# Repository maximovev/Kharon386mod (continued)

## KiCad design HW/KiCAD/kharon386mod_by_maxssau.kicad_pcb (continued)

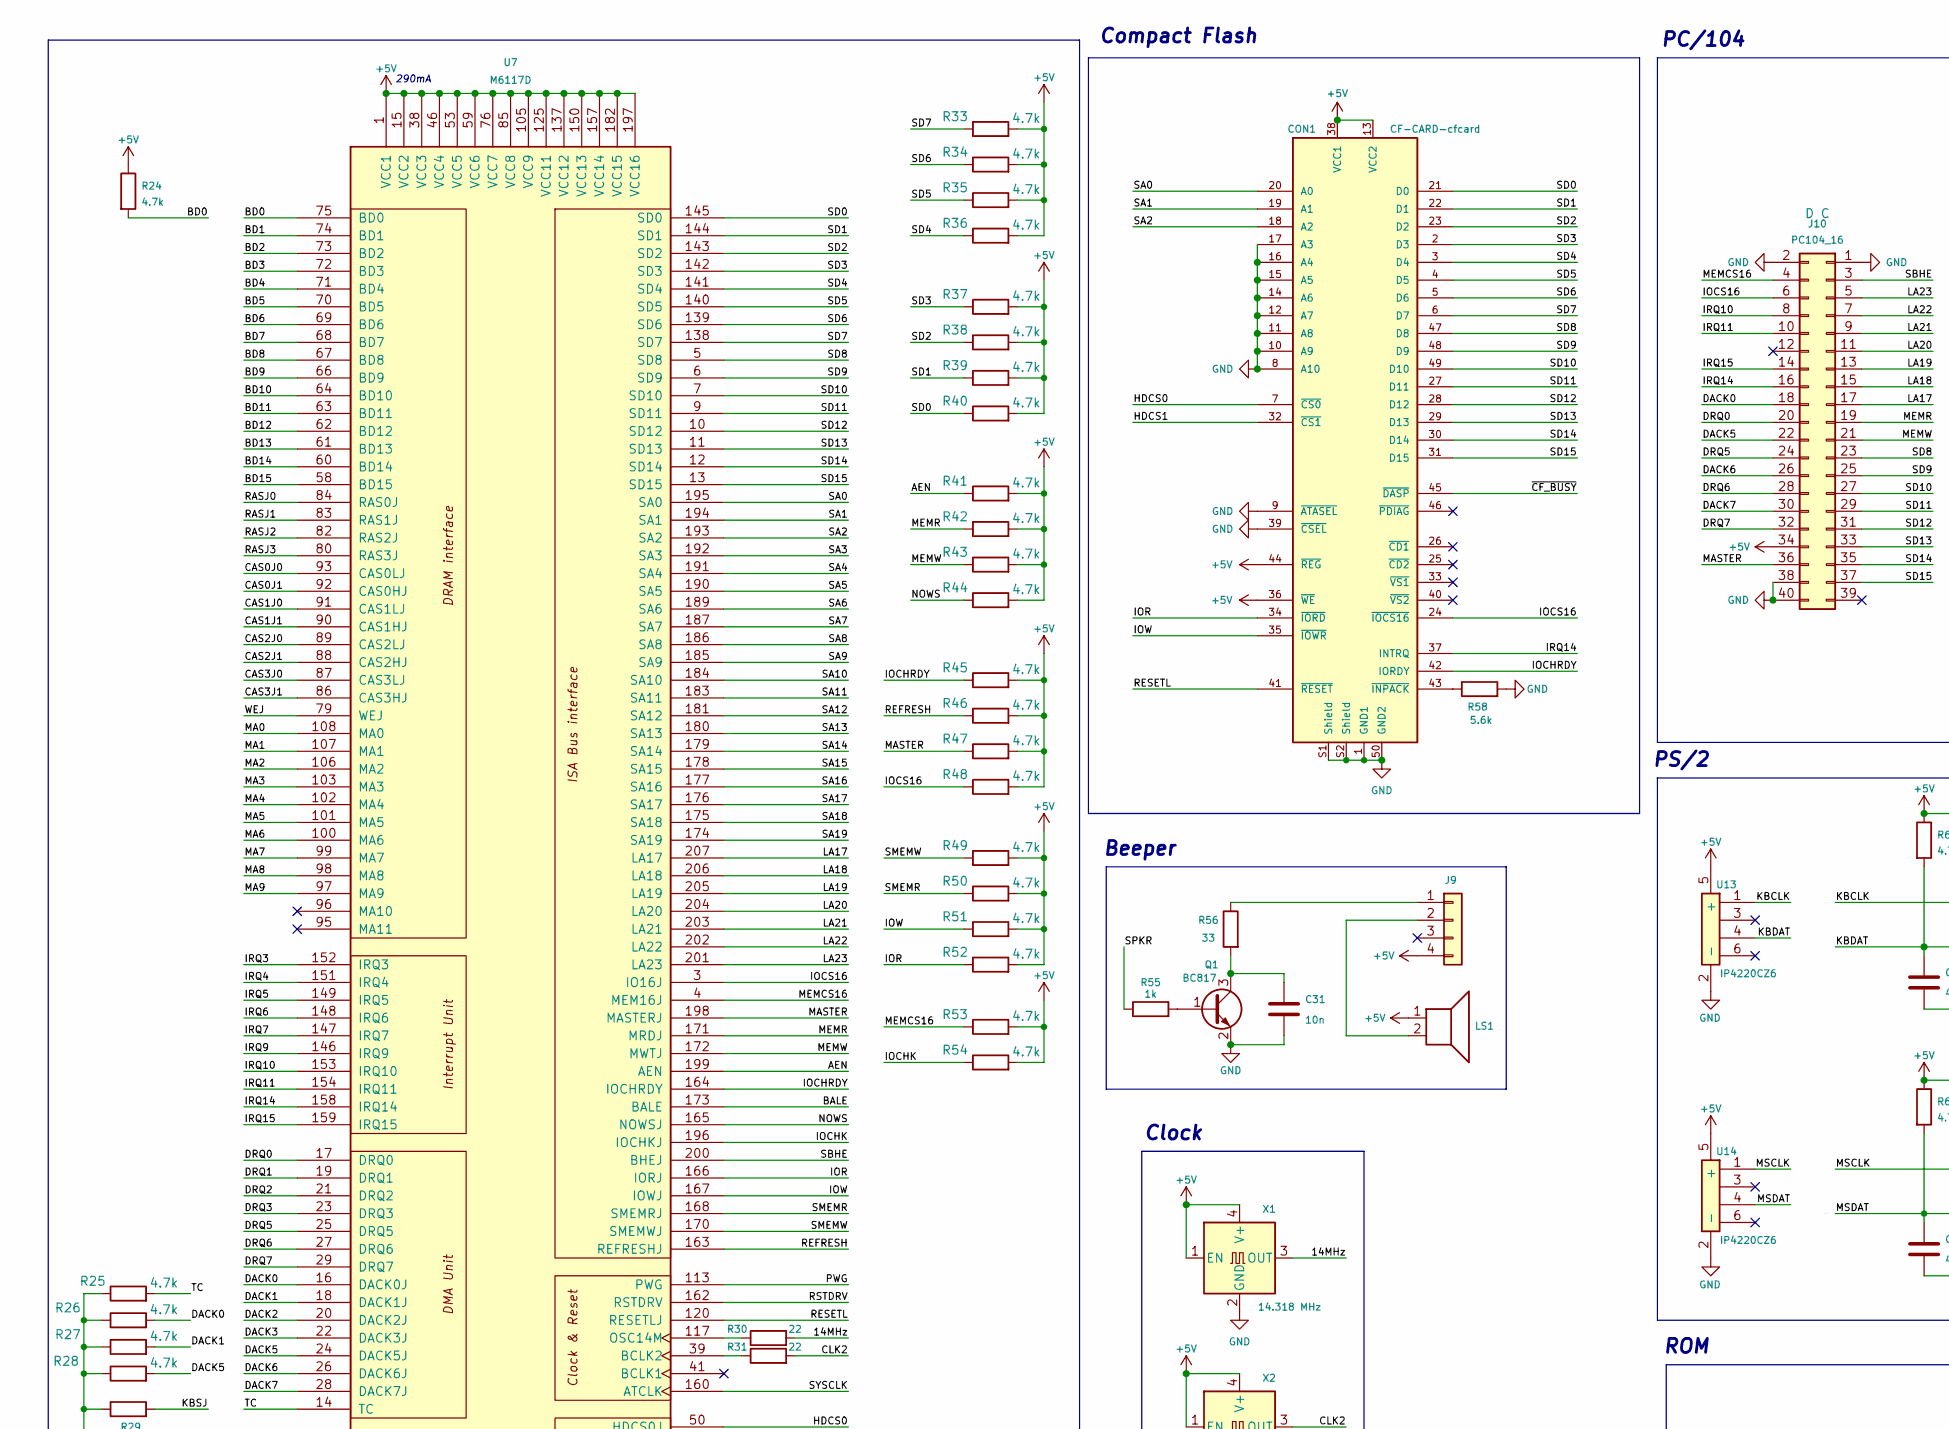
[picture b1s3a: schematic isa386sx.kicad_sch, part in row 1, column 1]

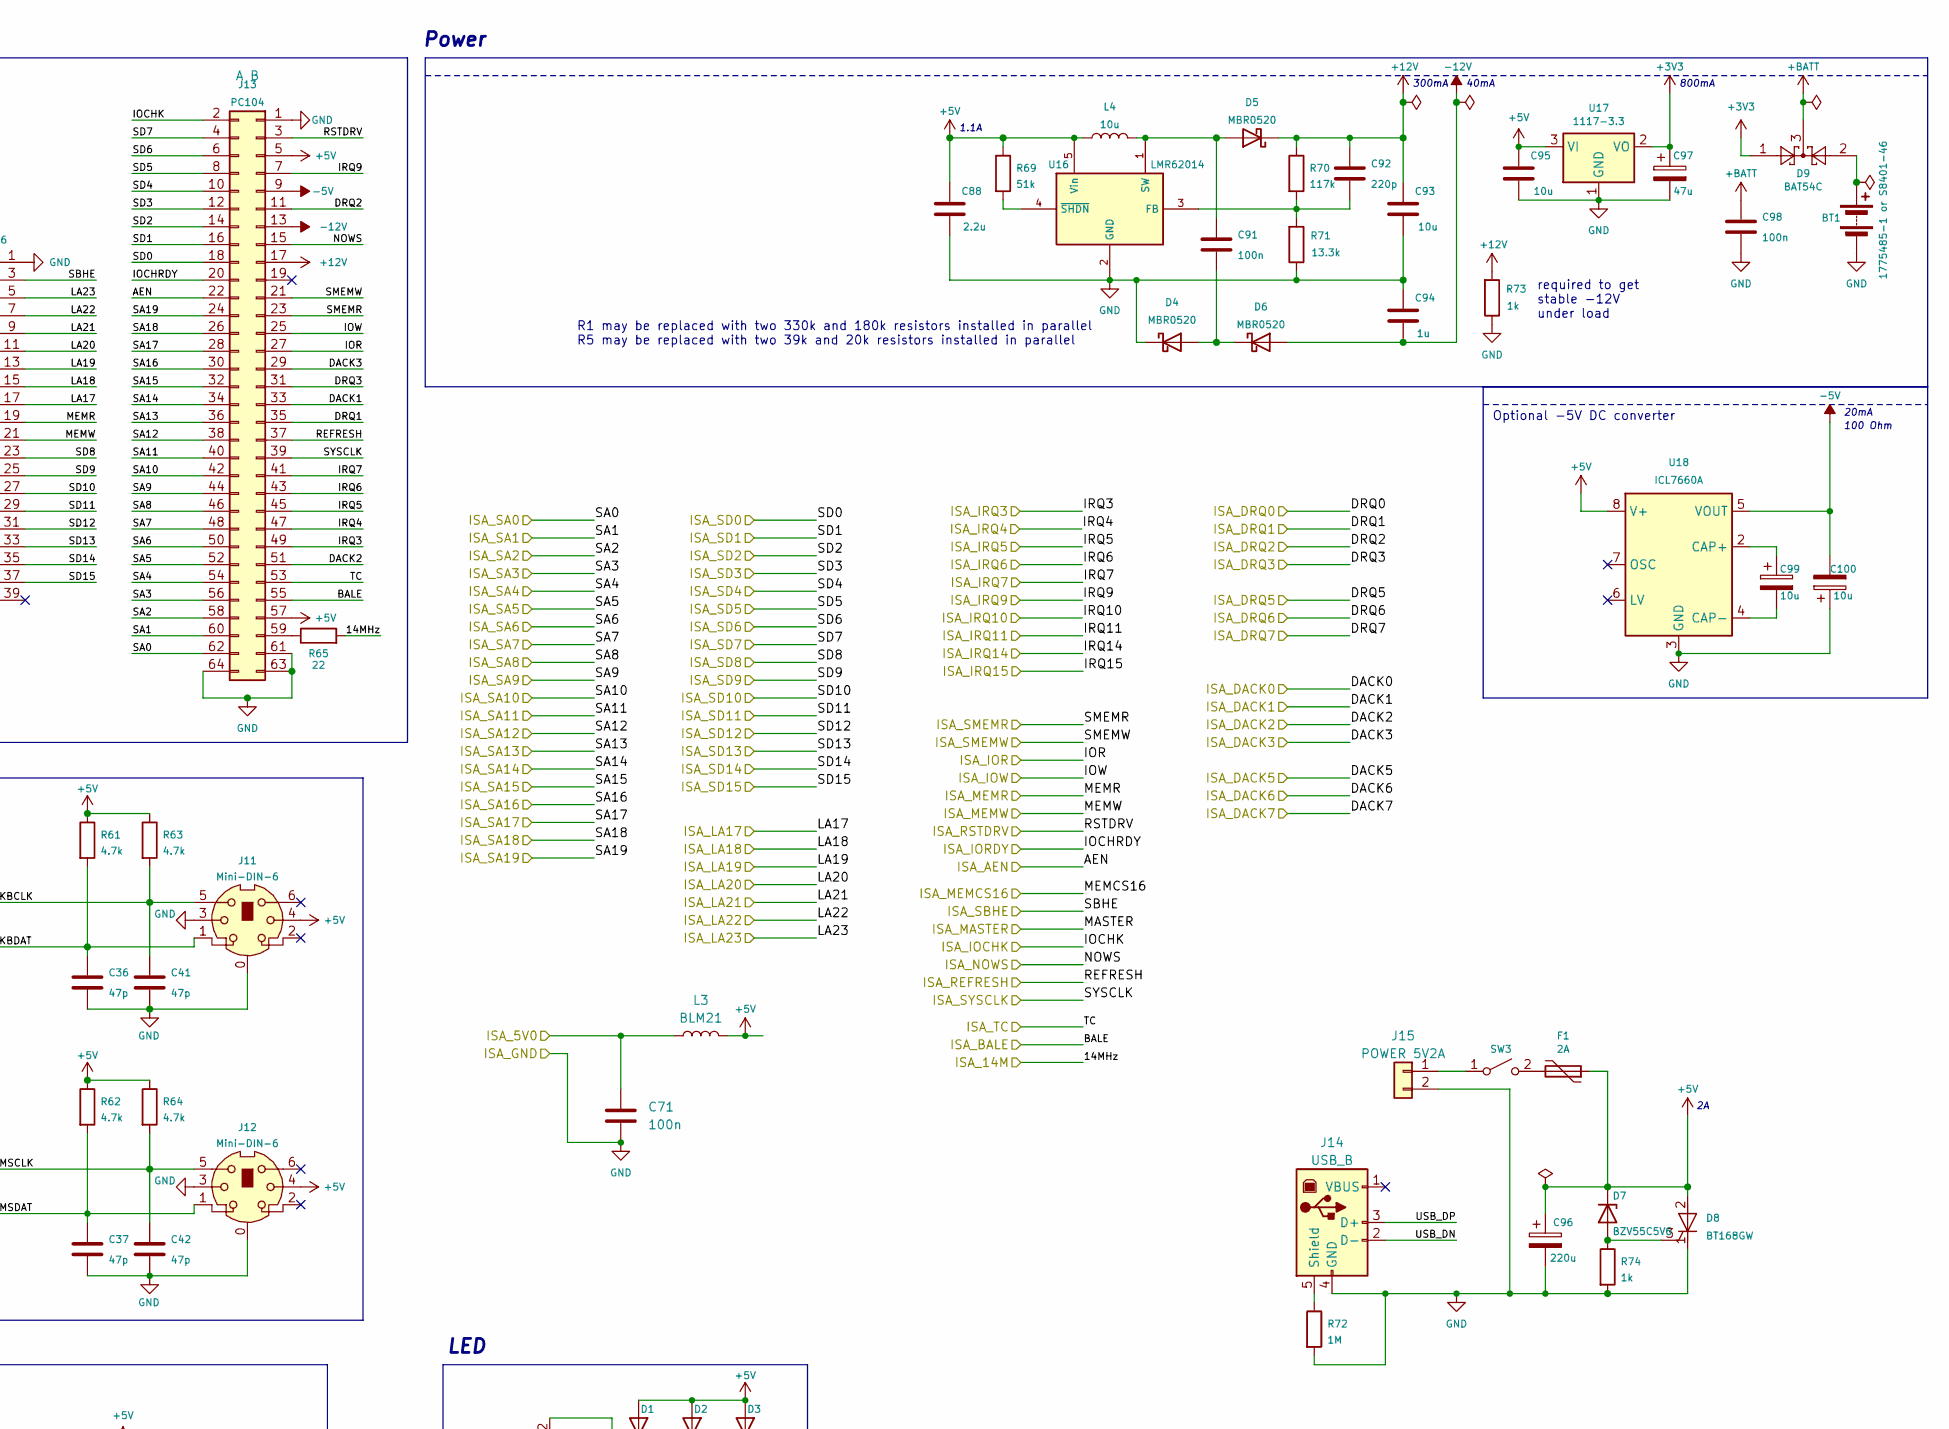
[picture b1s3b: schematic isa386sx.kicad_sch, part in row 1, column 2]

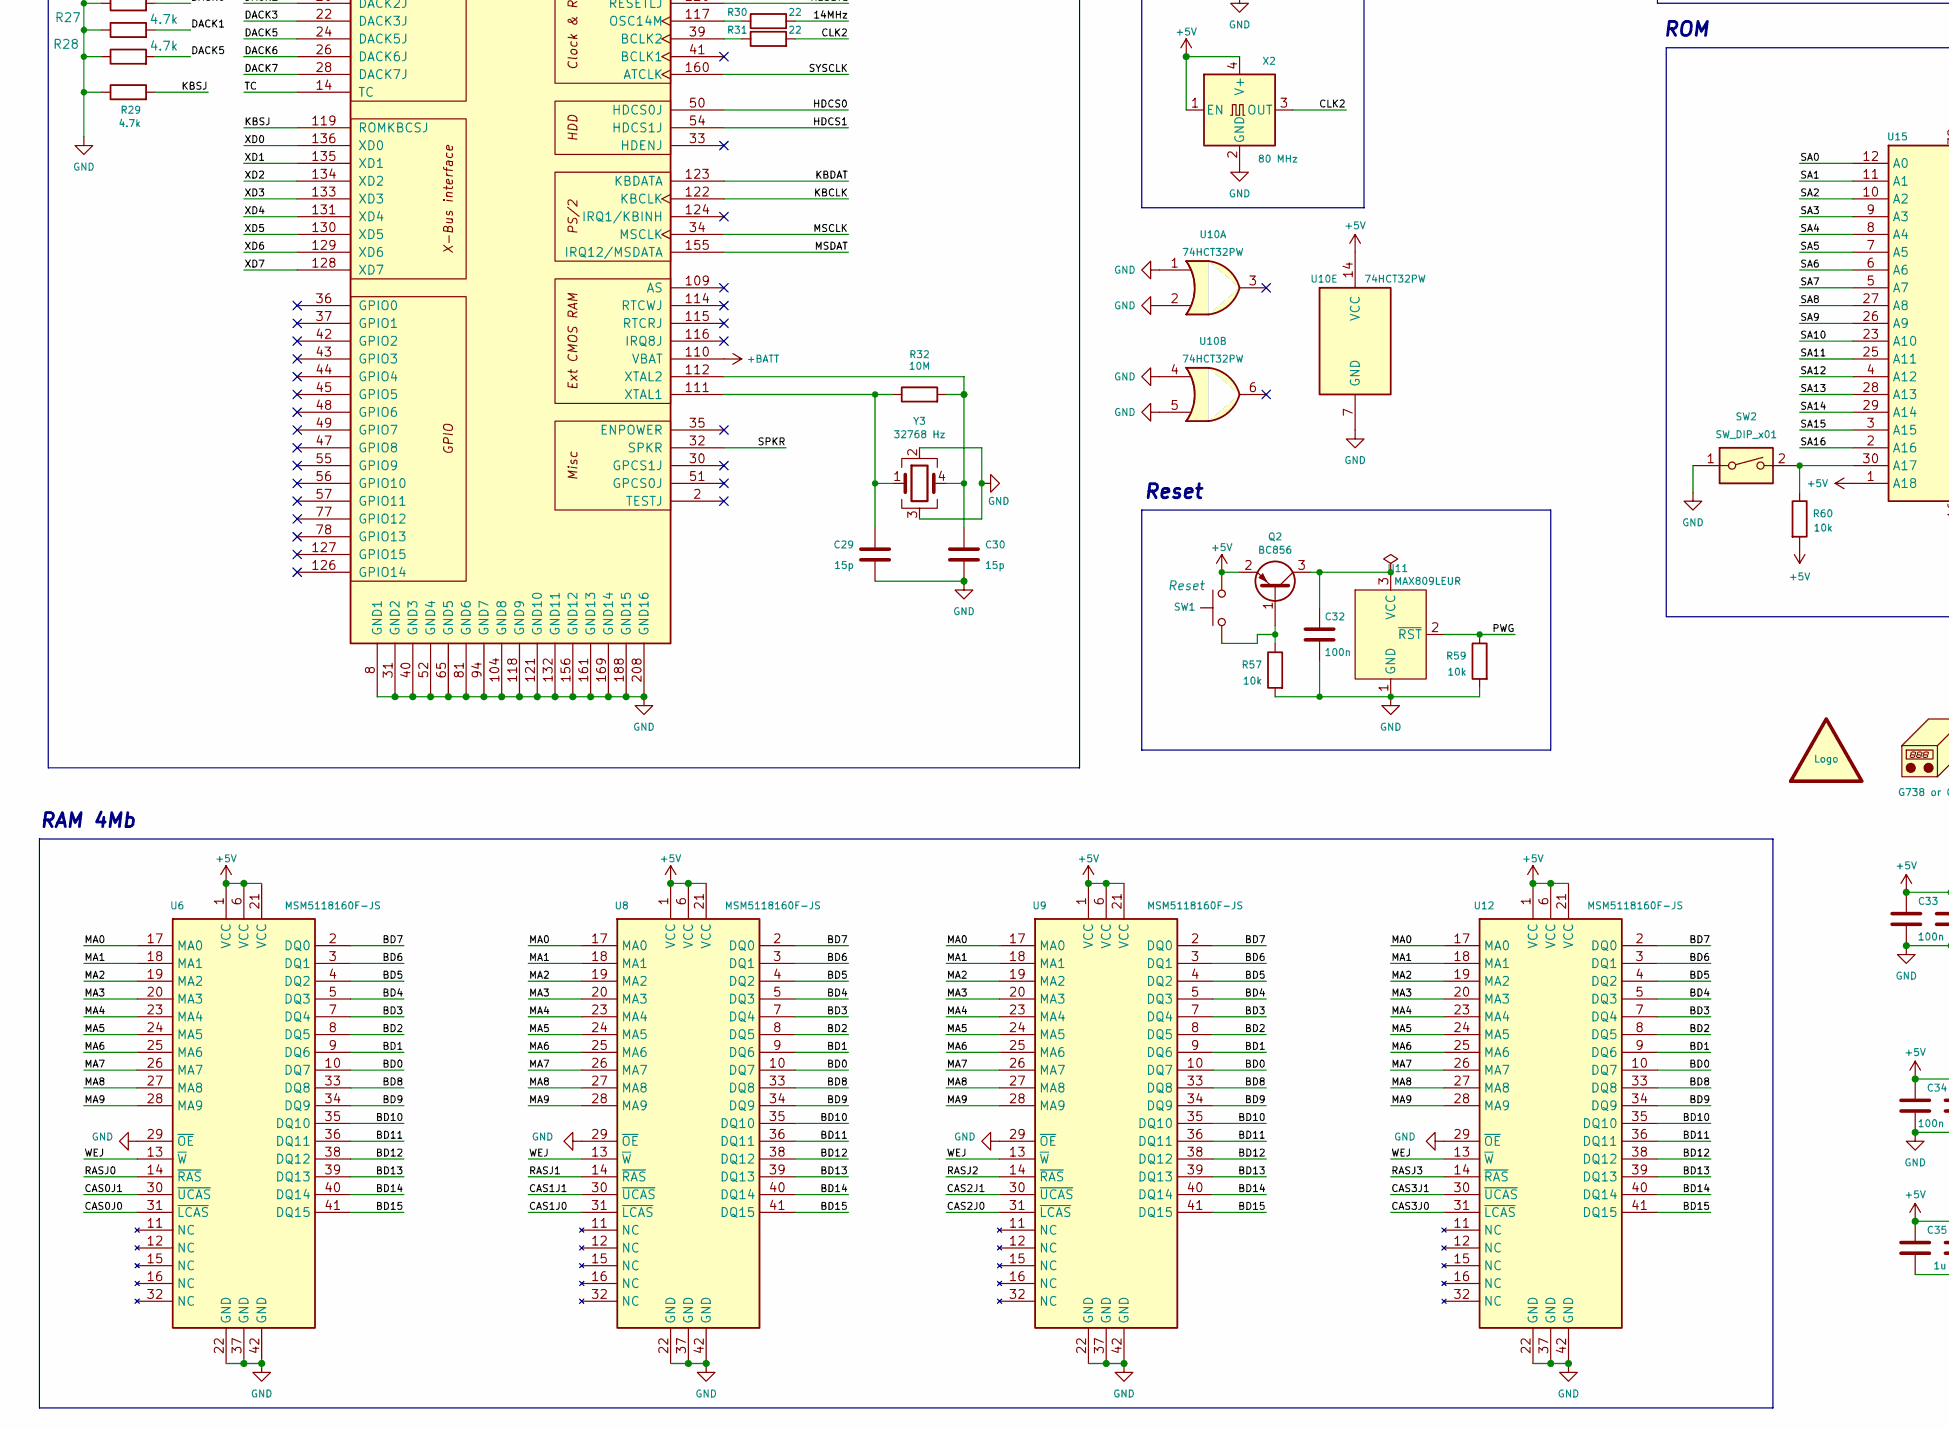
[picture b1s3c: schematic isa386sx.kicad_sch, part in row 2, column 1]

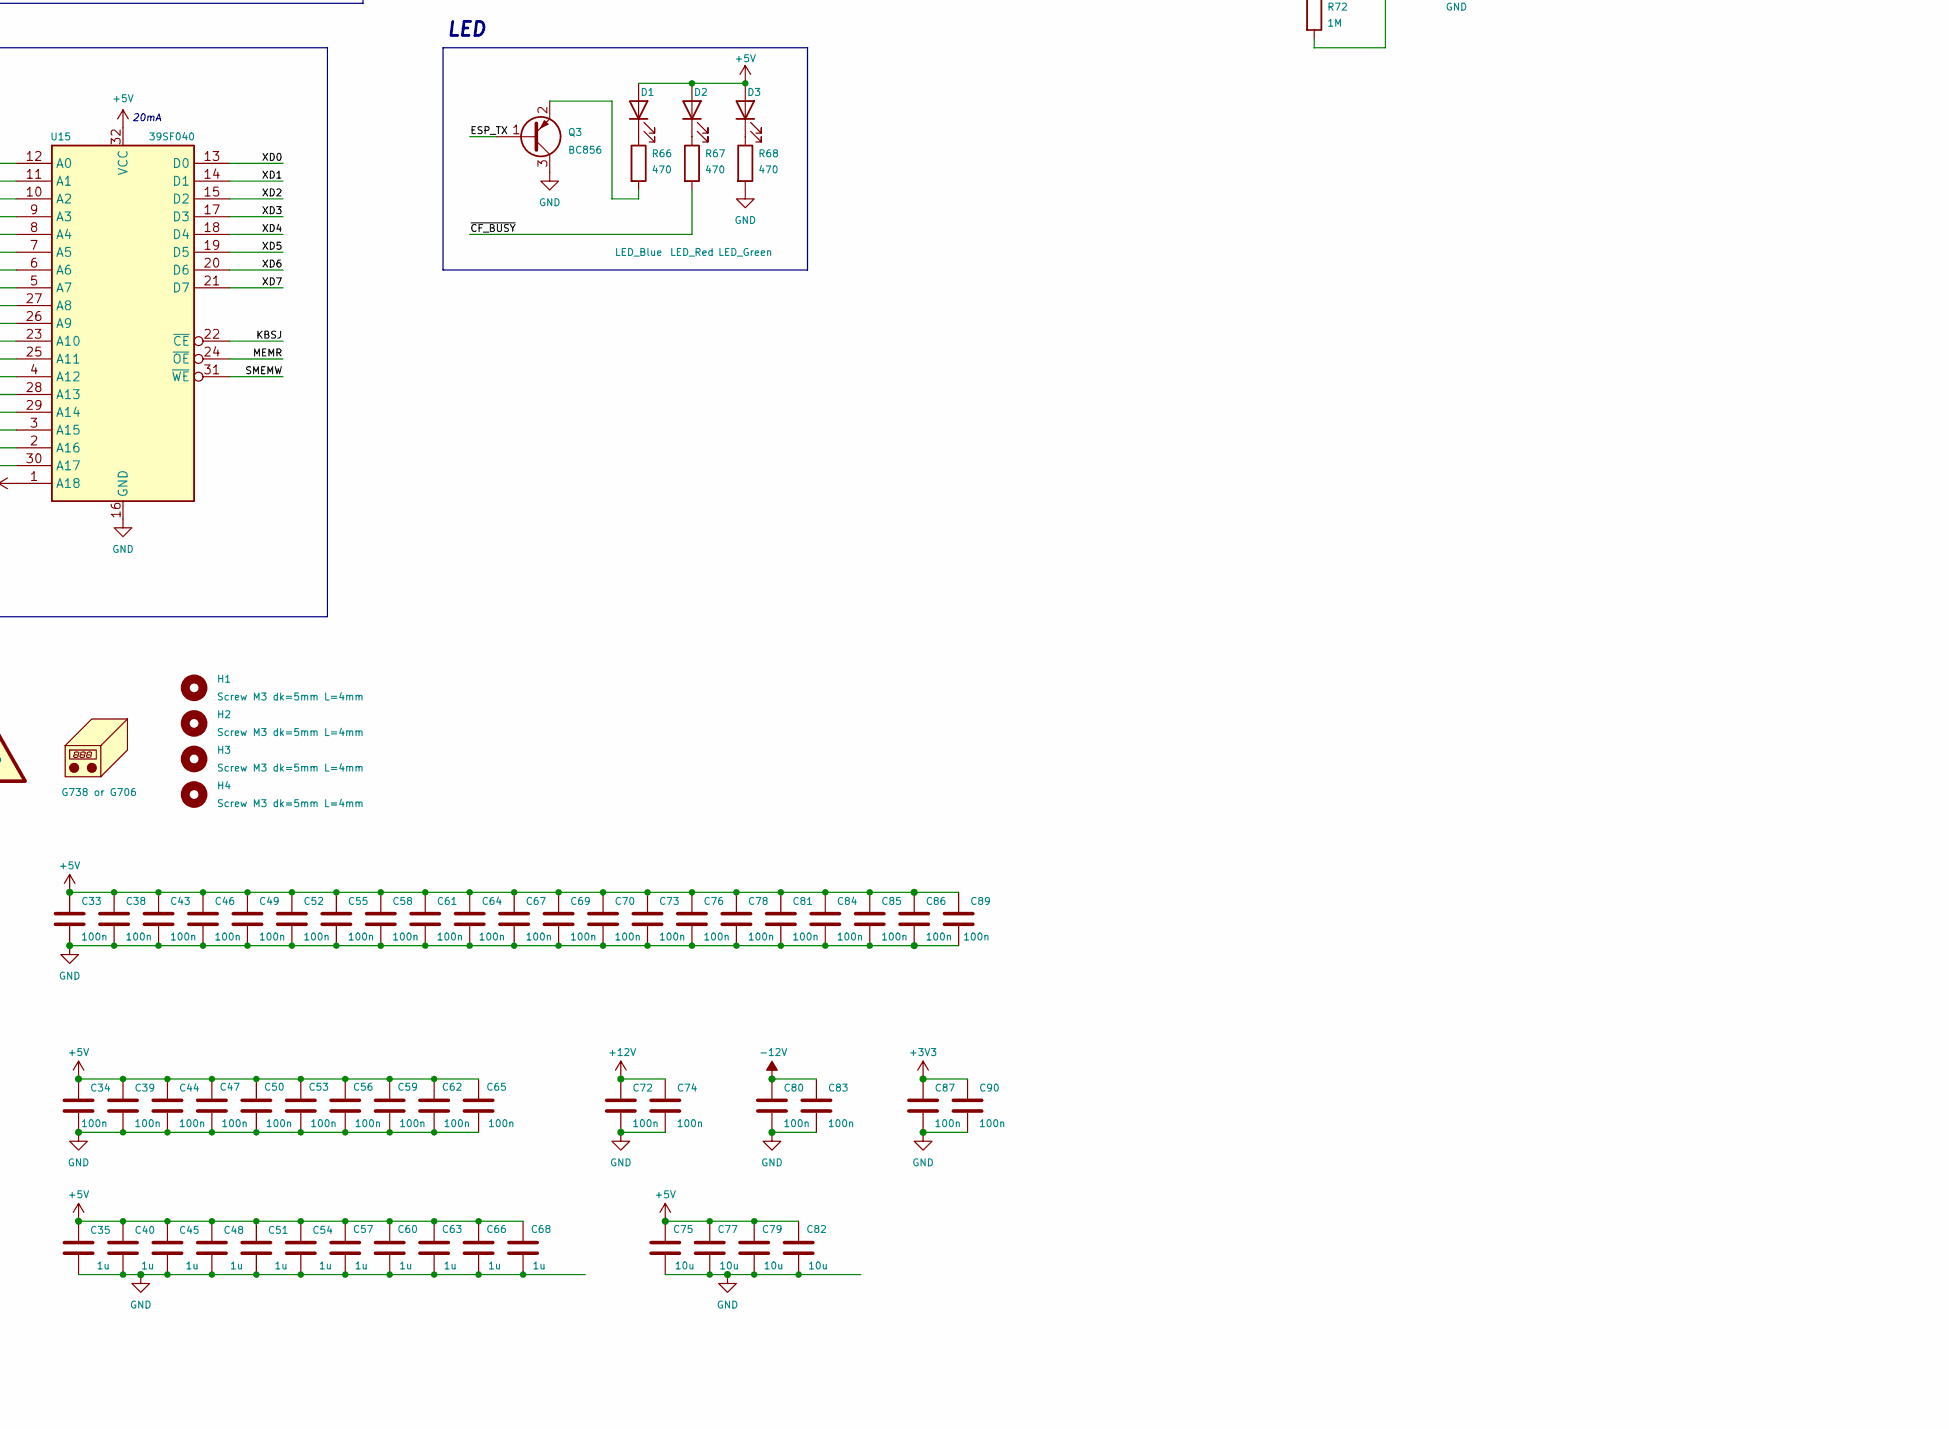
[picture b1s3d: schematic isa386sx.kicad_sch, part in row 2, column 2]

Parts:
BT1: 1775485-1 or S8401-46; BatteryHolder_MYOUNG_BS-07-A1BJ001_CR2032
C29, C30: 15p; C_0805_2012Metric_Pad1.18x1.45mm_HandSolder
C31: 10n; C_0805_2012Metric_Pad1.18x1.45mm_HandSolder
C32, C33, C34, C38, C39, C43, C44, C46, C47, C49, C50, C52, C53, C55, C56, C58, C59, C61, C62, C64, C65, C67, C69, C70, C71, C72, C73, C74, C76, C78, C80, C81, C83, C84, C85, C86, C87, C89, C90, C91, C98: 100n; C_0805_2012Metric_Pad1.18x1.45mm_HandSolder
C35, C40, C45, C48, C51, C54, C57, C60, C63, C66, C68, C94: 1u; C_0805_2012Metric_Pad1.18x1.45mm_HandSolder
C36, C37, C41, C42: 47p; C_0805_2012Metric_Pad1.18x1.45mm_HandSolder
C75, C77, C79, C82, C93, C95: 10u; C_0805_2012Metric_Pad1.18x1.45mm_HandSolder
C88: 2.2u; C_0805_2012Metric_Pad1.18x1.45mm_HandSolder
C92: 220p; C_0805_2012Metric_Pad1.18x1.45mm_HandSolder
C96: 220u; CP_EIA-7343-31_Kemet-D_Pad2.25x2.55mm_HandSolder
C97: 47u; CP_EIA-7343-31_Kemet-D_Pad2.25x2.55mm_HandSolder
C99, C100: 10u; CP_EIA-3528-21_Kemet-B_Pad1.50x2.35mm_HandSolder
CON1: CF-CARD-cfcard; TE_1734451-1-LONG
D1: LED_Blue; LED_D3.0mm_Horizontal_O1.27mm_Z6.0mm
D2: LED_Red; LED_D3.0mm_Horizontal_O1.27mm_Z6.0mm
D3: LED_Green; LED_D3.0mm_Horizontal_O1.27mm_Z6.0mm
D4, D5, D6: MBR0520; D_SOD-123
D7: BZV55C5V6; D_MiniMELF
D8: BT168GW; SOT-223-3_TabPin2
D9: BAT54C; SOT-23
F1: 2A; Fuse_1812_4532Metric_Pad1.30x3.40mm_HandSolder
H1, H2, H3, H4: Screw M3 dk=5mm L=4mm; MountingHole_3.2mm_M3_dk5.2mm_Mask
J9: Conn_01x04; PinHeader_1x04_P2.54mm_Vertical
J10: PC104_16; PinSocket_2x20_P2.54mm_Vertical
J11, J12: Mini-DIN-6; minidin-6
J13: PC104; PinSocket_2x32_P2.54mm_Vertical
J14: USB_B; USB_B_Lumberg_2411_02_Horizontal
J15: POWER 5V2A; TerminalBlock_bornier-2_P5.08mm
L3: BLM21; L_1210_3225Metric_Pad1.42x2.65mm_HandSolder
L4: 10u; L_7.3x7.3_H4.5
LOGO1: graphic; black-mage-12.5x8.6
LS1: Speaker; Buzzer_12x9.5RM7.6
N1: G738 or G706; G738
Q1: BC817; SOT-23
Q2, Q3: BC856; SOT-23
R24, R25, R26, R27, R28, R29, R33, R34, R35, R36, R37, R38, R39, R40, R41, R42, R43, R44, R45, R46, R47, R48, R49, R50, R51, R52, R53, R54, R61, R62, R63, R64: 4.7k; R_0805_2012Metric_Pad1.20x1.40mm_HandSolder
R30, R31, R65: 22; R_0805_2012Metric_Pad1.20x1.40mm_HandSolder
R32: 10M; R_0805_2012Metric_Pad1.20x1.40mm_HandSolder
R55, R73, R74: 1k; R_0805_2012Metric_Pad1.20x1.40mm_HandSolder
R56: 33; R_0805_2012Metric_Pad1.20x1.40mm_HandSolder
R57, R59, R60: 10k; R_0805_2012Metric_Pad1.20x1.40mm_HandSolder
R58: 5.6k; R_0805_2012Metric_Pad1.20x1.40mm_HandSolder
R66, R67, R68: 470; R_0805_2012Metric_Pad1.20x1.40mm_HandSolder
R69: 51k; R_0805_2012Metric_Pad1.20x1.40mm_HandSolder
R70: 117k; R_0805_2012Metric_Pad1.20x1.40mm_HandSolder
R71: 13.3k; R_0805_2012Metric_Pad1.20x1.40mm_HandSolder
R72: 1M; R_0805_2012Metric_Pad1.20x1.40mm_HandSolder
SW1: SW_Push; SW_Tactile_SPST_Angled_PTS645Vx83-2LFS
SW2: SW_DIP_x01; SW_DIP_SPSTx01_Slide_6.7x4.1mm_W7.62mm_P2.54mm_LowProfile
SW3: Jumper / Pin header 1x2 Pitch=2.54mm; Molex_KK-254_AE-6410-02A_1x02_P2.54mm_Vertical
U6, U8, U9, U12: MSM5118160F-JS; SOJ-42
U7: M6117D; PQFP-208_28x28mm_P0.5mm
U10: 74HCT32PW; TSSOP-14_4.4x5mm_P0.65mm
U11: MAX809LEUR; SOT-23
U13, U14: IP4220CZ6; TSOP-6_1.65x3.05mm_P0.95mm
U15: 39SF040; PLCC-32_11.4x14.0mm_P1.27mm-longpads
U16: LMR62014; SOT-23-5_HandSoldering
U17: 1117-3.3; SOT-223-3_TabPin2
U18: ICL7660A; SOIC-8_3.9x4.9mm_P1.27mm
X1: 14.318 MHz; Oscillator_SMD_Abracon_ASE-4Pin_3.2x2.5mm_HandSoldering
X2: 80 MHz; Oscillator_SMD_Abracon_ASE-4Pin_3.2x2.5mm_HandSoldering
Y3: 32768 Hz; Crystal_SMD_SeikoEpson_MC306-4Pin_8.0x3.2mm_HandSoldering

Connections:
+3V3: C87.2, C90.2, C97.1, D9.1, U17.2 (VO); also elsewhere on the board
+5V: C33.2, C34.2, C35.2, C38.2, C39.2, C40.2, C43.2, C44.2, C45.2, C46.2, C47.1, C48.2, C49.2, C50.1, C51.2, C52.2, C53.1, C54.2, C55.2, C56.1, C57.1, C58.2, C59.1, C60.1, C61.2, C62.1, C63.1, C64.2, C65.1, C66.1, C67.2, C68.1, C69.2, C70.2, C73.2, C75.1, C76.2, C77.1, C78.2, C79.1, C81.2, C82.1, C84.2, C85.2, C86.2, C88.2, C89.2, C95.2, C96.1, CON1.13 (VCC2), CON1.36 (~WE), CON1.38 (VCC1), CON1.44 (~REG), D1.2 (A), D2.2 (A), D3.2 (A), D7.1 (K), D8.2 (A), F1.1, J9.4, J10.34, J11.4, J12.4, J13.5, J13.57, L3.2, L4.1, LS1.1, Q2.2 (E), R24.1, R33.2, R34.2, R35.2, R36.2, R37.2, R38.2, R39.2, R40.2, R41.2, R42.2, R43.2, R44.2, R45.2, R46.2, R47.2, R48.2, R49.2, R50.2, R51.2, R52.2, R53.2, R54.2, R60.2, R61.1, R62.1, R63.1, R64.1, R69.1, SW1.1, U6.1 (VCC), U6.6 (VCC), U6.21 (VCC), U7.1 (VCC1), U7.15 (VCC2), U7.38 (VCC3), U7.46 (VCC4), U7.53 (VCC5), U7.59 (VCC6), U7.76 (VCC7), U7.85 (VCC8), U7.105 (VCC9), U7.125 (VCC11), U7.137 (VCC12), U7.150 (VCC13), U7.157 (VCC14), U7.182 (VCC15), U7.197 (VCC16), U8.1 (VCC), U8.6 (VCC), U8.21 (VCC), U9.1 (VCC), U9.6 (VCC), U9.21 (VCC), U10.14 (VCC), U12.1 (VCC), U12.6 (VCC), U12.21 (VCC), U13.5 (+), U14.5 (+), U15.1 (A18), U15.32 (VCC), U16.5 (Vin), U17.3 (VI), U18.8 (V+), X1.1 (EN), X1.4 (V+), X2.1 (EN), X2.4 (V+); also elsewhere on the board
+12V: C72.2, C74.2, C92.1, C93.2, D5.1 (K), J13.17, R70.1, R73.2; also elsewhere on the board
+BATT: C98.1, D9.3, U7.110 (VBAT)
-5V: C100.2, J13.9, U18.5 (VOUT)
-12V: C80.2, C83.2, C94.1, D6.2 (A), J13.13; also elsewhere on the board
/B_ISA_5V0: C71.1, L3.1; also elsewhere on the board
/B_ISA_14M: R30.2, R65.2, X1.3 (OUT); also elsewhere on the board
/B_ISA_A0: CON1.20 (A0), J13.62, U7.195 (SA0), U15.12 (A0); also elsewhere on the board
/B_ISA_A1: CON1.19 (A1), J13.60, U7.194 (SA1), U15.11 (A1); also elsewhere on the board
/B_ISA_A2: CON1.18 (A2), J13.58, U7.193 (SA2), U15.10 (A2); also elsewhere on the board
/B_ISA_A3: J13.56, U7.192 (SA3), U15.9 (A3); also elsewhere on the board
/B_ISA_A4: J13.54, U7.191 (SA4), U15.8 (A4); also elsewhere on the board
/B_ISA_A5: J13.52, U7.190 (SA5), U15.7 (A5); also elsewhere on the board
/B_ISA_A6: J13.50, U7.189 (SA6), U15.6 (A6); also elsewhere on the board
/B_ISA_A7: J13.48, U7.187 (SA7), U15.5 (A7); also elsewhere on the board
/B_ISA_A8: J13.46, U7.186 (SA8), U15.27 (A8); also elsewhere on the board
/B_ISA_A9: J13.44, U7.185 (SA9), U15.26 (A9); also elsewhere on the board
/B_ISA_A10: J13.42, U7.184 (SA10), U15.23 (A10); also elsewhere on the board
/B_ISA_A11: J13.40, U7.183 (SA11), U15.25 (A11); also elsewhere on the board
/B_ISA_A12: J13.38, U7.181 (SA12), U15.4 (A12); also elsewhere on the board
/B_ISA_A13: J13.36, U7.180 (SA13), U15.28 (A13); also elsewhere on the board
/B_ISA_A14: J13.34, U7.179 (SA14), U15.29 (A14); also elsewhere on the board
/B_ISA_A15: J13.32, U7.178 (SA15), U15.3 (A15); also elsewhere on the board
/B_ISA_A16: J13.30, U7.177 (SA16), U15.2 (A16); also elsewhere on the board
/B_ISA_A17: J13.28, U7.176 (SA17); also elsewhere on the board
/B_ISA_A18: J13.26, U7.175 (SA18); also elsewhere on the board
/B_ISA_A19: J13.24, U7.174 (SA19); also elsewhere on the board
/B_ISA_AEN: J13.22, R41.1, U7.199 (AEN); also elsewhere on the board
/B_ISA_BALE: J13.55, U7.173 (BALE); also elsewhere on the board
/B_ISA_D0: CON1.21 (D0), J13.18, R40.1, U7.145 (SD0); also elsewhere on the board
/B_ISA_D1: CON1.22 (D1), J13.16, R39.1, U7.144 (SD1); also elsewhere on the board
/B_ISA_D2: CON1.23 (D2), J13.14, R38.1, U7.143 (SD2); also elsewhere on the board
/B_ISA_D3: CON1.2 (D3), J13.12, R37.1, U7.142 (SD3); also elsewhere on the board
/B_ISA_D4: CON1.3 (D4), J13.10, R36.1, U7.141 (SD4); also elsewhere on the board
/B_ISA_D5: CON1.4 (D5), J13.8, R35.1, U7.140 (SD5); also elsewhere on the board
/B_ISA_D6: CON1.5 (D6), J13.6, R34.1, U7.139 (SD6); also elsewhere on the board
/B_ISA_D7: CON1.6 (D7), J13.4, R33.1, U7.138 (SD7); also elsewhere on the board
/B_ISA_D8: CON1.47 (D8), J10.23, U7.5 (SD8); also elsewhere on the board
/B_ISA_D9: CON1.48 (D9), J10.25, U7.6 (SD9); also elsewhere on the board
/B_ISA_D10: CON1.49 (D10), J10.27, U7.7 (SD10); also elsewhere on the board
/B_ISA_D11: CON1.27 (D11), J10.29, U7.9 (SD11); also elsewhere on the board
/B_ISA_D12: CON1.28 (D12), J10.31, U7.10 (SD12); also elsewhere on the board
/B_ISA_D13: CON1.29 (D13), J10.33, U7.11 (SD13); also elsewhere on the board
/B_ISA_D14: CON1.30 (D14), J10.35, U7.12 (SD14); also elsewhere on the board
/B_ISA_D15: CON1.31 (D15), J10.37, U7.13 (SD15); also elsewhere on the board
/B_ISA_DACK0: J10.18, R26.2, U7.16 (DACK0J); also elsewhere on the board
/B_ISA_DACK1: J13.33, R27.2, U7.18 (DACK1J); also elsewhere on the board
/B_ISA_DACK2: J13.51, U7.20 (DACK2J)
/B_ISA_DACK3: J13.29, U7.22 (DACK3J); also elsewhere on the board
/B_ISA_DACK5: J10.22, R28.2, U7.24 (DACK5J); also elsewhere on the board
/B_ISA_DACK6: J10.26, U7.26 (DACK6J)
/B_ISA_DACK7: J10.30, U7.28 (DACK7J)
/B_ISA_DRQ0: J10.20, U7.17 (DRQ0); also elsewhere on the board
/B_ISA_DRQ1: J13.35, U7.19 (DRQ1); also elsewhere on the board
/B_ISA_DRQ2: J13.11, U7.21 (DRQ2)
/B_ISA_DRQ3: J13.31, U7.23 (DRQ3); also elsewhere on the board
/B_ISA_DRQ5: J10.24, U7.25 (DRQ5); also elsewhere on the board
/B_ISA_DRQ6: J10.28, U7.27 (DRQ6)
/B_ISA_DRQ7: J10.32, U7.29 (DRQ7)
/B_ISA_IOCHK: J13.2, R54.1, U7.196 (IOCHKJ); also elsewhere on the board
/B_ISA_IOR: CON1.34 (~IORD), J13.27, R52.1, U7.166 (IORJ); also elsewhere on the board
/B_ISA_IORDY: CON1.42 (IORDY), J13.20, R45.1, U7.164 (IOCHRDY); also elsewhere on the board
/B_ISA_IOW: CON1.35 (~IOWR), J13.25, R51.1, U7.167 (IOWJ); also elsewhere on the board
/B_ISA_IRQ3: J13.49, U7.152 (IRQ3); also elsewhere on the board
/B_ISA_IRQ4: J13.47, U7.151 (IRQ4); also elsewhere on the board
/B_ISA_IRQ5: J13.45, U7.149 (IRQ5); also elsewhere on the board
/B_ISA_IRQ6: J13.43, U7.148 (IRQ6)
/B_ISA_IRQ7: J13.41, U7.147 (IRQ7); also elsewhere on the board
/B_ISA_IRQ9: J13.7, U7.146 (IRQ9); also elsewhere on the board
/B_ISA_IRQ10: J10.8, U7.153 (IRQ10); also elsewhere on the board
/B_ISA_IRQ11: J10.10, U7.154 (IRQ11); also elsewhere on the board
/B_ISA_IRQ14: CON1.37 (INTRQ), J10.16, U7.158 (IRQ14)
/B_ISA_IRQ15: J10.14, U7.159 (IRQ15)
/B_ISA_LA17: J10.17, U7.207 (LA17); also elsewhere on the board
/B_ISA_LA18: J10.15, U7.206 (LA18); also elsewhere on the board
/B_ISA_LA19: J10.13, U7.205 (LA19); also elsewhere on the board
/B_ISA_LA20: J10.11, U7.204 (LA20); also elsewhere on the board
/B_ISA_LA21: J10.9, U7.203 (LA21); also elsewhere on the board
/B_ISA_LA22: J10.7, U7.202 (LA22); also elsewhere on the board
/B_ISA_LA23: J10.5, U7.201 (LA23); also elsewhere on the board
/B_ISA_MEMCS16: J10.4, R53.1, U7.4 (MEM16J); also elsewhere on the board
/B_ISA_MEMR: J10.19, R42.1, U7.171 (MRDJ), U15.24 (~OE)
/B_ISA_MEMW: J10.21, R43.1, U7.172 (MWTJ)
/B_ISA_REFRESH: J13.37, R46.1, U7.163 (REFRESHJ); also elsewhere on the board
/B_ISA_RSTDRV: J13.3, U7.162 (RSTDRV); also elsewhere on the board
/B_ISA_SBHE: J10.3, U7.200 (BHEJ); also elsewhere on the board
/B_ISA_SMEMR: J13.23, R50.1, U7.168 (SMEMRJ); also elsewhere on the board
/B_ISA_SMEMW: J13.21, R49.1, U7.170 (SMEMWJ), U15.31 (~WE); also elsewhere on the board
/B_ISA_TC: J13.53, R25.2, U7.14 (TC)
/ISA_386SX_BOARD/BD0: R24.2, U6.10 (DQ7), U7.75 (BD0), U8.10 (DQ7), U9.10 (DQ7), U12.10 (DQ7)
/ISA_386SX_BOARD/BD1: U6.9 (DQ6), U7.74 (BD1), U8.9 (DQ6), U9.9 (DQ6), U12.9 (DQ6)
/ISA_386SX_BOARD/BD2: U6.8 (DQ5), U7.73 (BD2), U8.8 (DQ5), U9.8 (DQ5), U12.8 (DQ5)
/ISA_386SX_BOARD/BD3: U6.7 (DQ4), U7.72 (BD3), U8.7 (DQ4), U9.7 (DQ4), U12.7 (DQ4)
/ISA_386SX_BOARD/BD4: U6.5 (DQ3), U7.71 (BD4), U8.5 (DQ3), U9.5 (DQ3), U12.5 (DQ3)
/ISA_386SX_BOARD/BD5: U6.4 (DQ2), U7.70 (BD5), U8.4 (DQ2), U9.4 (DQ2), U12.4 (DQ2)
/ISA_386SX_BOARD/BD6: U6.3 (DQ1), U7.69 (BD6), U8.3 (DQ1), U9.3 (DQ1), U12.3 (DQ1)
/ISA_386SX_BOARD/BD7: U6.2 (DQ0), U7.68 (BD7), U8.2 (DQ0), U9.2 (DQ0), U12.2 (DQ0)
/ISA_386SX_BOARD/BD8: U6.33 (DQ8), U7.67 (BD8), U8.33 (DQ8), U9.33 (DQ8), U12.33 (DQ8)
/ISA_386SX_BOARD/BD9: U6.34 (DQ9), U7.66 (BD9), U8.34 (DQ9), U9.34 (DQ9), U12.34 (DQ9)
/ISA_386SX_BOARD/BD10: U6.35 (DQ10), U7.64 (BD10), U8.35 (DQ10), U9.35 (DQ10), U12.35 (DQ10)
/ISA_386SX_BOARD/BD11: U6.36 (DQ11), U7.63 (BD11), U8.36 (DQ11), U9.36 (DQ11), U12.36 (DQ11)
/ISA_386SX_BOARD/BD12: U6.38 (DQ12), U7.62 (BD12), U8.38 (DQ12), U9.38 (DQ12), U12.38 (DQ12)
/ISA_386SX_BOARD/BD13: U6.39 (DQ13), U7.61 (BD13), U8.39 (DQ13), U9.39 (DQ13), U12.39 (DQ13)
/ISA_386SX_BOARD/BD14: U6.40 (DQ14), U7.60 (BD14), U8.40 (DQ14), U9.40 (DQ14), U12.40 (DQ14)
/ISA_386SX_BOARD/BD15: U6.41 (DQ15), U7.58 (BD15), U8.41 (DQ15), U9.41 (DQ15), U12.41 (DQ15)
/ISA_386SX_BOARD/CAS0J0: U6.31 (~LCAS), U7.93 (CAS0LJ)
/ISA_386SX_BOARD/CAS0J1: U6.30 (~UCAS), U7.92 (CAS0HJ)
/ISA_386SX_BOARD/CAS1J0: U7.91 (CAS1LJ), U8.31 (~LCAS)
/ISA_386SX_BOARD/CAS1J1: U7.90 (CAS1HJ), U8.30 (~UCAS)
/ISA_386SX_BOARD/CAS2J0: U7.89 (CAS2LJ), U9.31 (~LCAS)
/ISA_386SX_BOARD/CAS2J1: U7.88 (CAS2HJ), U9.30 (~UCAS)
/ISA_386SX_BOARD/CAS3J0: U7.87 (CAS3LJ), U12.31 (~LCAS)
/ISA_386SX_BOARD/CAS3J1: U7.86 (CAS3HJ), U12.30 (~UCAS)
/ISA_386SX_BOARD/CLK2: R31.2, X2.3 (OUT)
/ISA_386SX_BOARD/ESP_TX: Q3.1 (B)
/ISA_386SX_BOARD/HDCS0: CON1.7 (~CS0), U7.50 (HDCS0J)
/ISA_386SX_BOARD/HDCS1: CON1.32 (~CS1), U7.54 (HDCS1J)
/ISA_386SX_BOARD/IOCS16: CON1.24 (~IOCS16), J10.6, R48.1, U7.3 (IO16J)
/ISA_386SX_BOARD/KBCLK: C41.1, J11.5, R63.2, U7.122 (KBCLK), U13.1
/ISA_386SX_BOARD/KBDAT: C36.1, J11.1, R61.2, U7.123 (KBDATA), U13.4
/ISA_386SX_BOARD/KBSJ: R29.2, U7.119 (ROMKBCSJ), U15.22 (~CE)
/ISA_386SX_BOARD/MA0: U6.17 (MA0), U7.108 (MA0), U8.17 (MA0), U9.17 (MA0), U12.17 (MA0)
/ISA_386SX_BOARD/MA1: U6.18 (MA1), U7.107 (MA1), U8.18 (MA1), U9.18 (MA1), U12.18 (MA1)
/ISA_386SX_BOARD/MA2: U6.19 (MA2), U7.106 (MA2), U8.19 (MA2), U9.19 (MA2), U12.19 (MA2)
/ISA_386SX_BOARD/MA3: U6.20 (MA3), U7.103 (MA3), U8.20 (MA3), U9.20 (MA3), U12.20 (MA3)
/ISA_386SX_BOARD/MA4: U6.23 (MA4), U7.102 (MA4), U8.23 (MA4), U9.23 (MA4), U12.23 (MA4)
/ISA_386SX_BOARD/MA5: U6.24 (MA5), U7.101 (MA5), U8.24 (MA5), U9.24 (MA5), U12.24 (MA5)
/ISA_386SX_BOARD/MA6: U6.25 (MA6), U7.100 (MA6), U8.25 (MA6), U9.25 (MA6), U12.25 (MA6)
/ISA_386SX_BOARD/MA7: U6.26 (MA7), U7.99 (MA7), U8.26 (MA7), U9.26 (MA7), U12.26 (MA7)
/ISA_386SX_BOARD/MA8: U6.27 (MA8), U7.98 (MA8), U8.27 (MA8), U9.27 (MA8), U12.27 (MA8)
/ISA_386SX_BOARD/MA9: U6.28 (MA9), U7.97 (MA9), U8.28 (MA9), U9.28 (MA9), U12.28 (MA9)
/ISA_386SX_BOARD/MASTER: J10.36, R47.1, U7.198 (MASTERJ)
/ISA_386SX_BOARD/MSCLK: C42.1, J12.5, R64.2, U7.34 (MSCLK), U14.1
/ISA_386SX_BOARD/MSDAT: C37.1, J12.1, R62.2, U7.155 (IRQ12/MSDATA), U14.4
/ISA_386SX_BOARD/NOWS: J13.15, R44.1, U7.165 (NOWSJ)
/ISA_386SX_BOARD/PWG: R59.1, U7.113 (PWG), U11.2 (~RST)
/ISA_386SX_BOARD/RASJ0: U6.14 (~RAS), U7.84 (RAS0J)
/ISA_386SX_BOARD/RASJ1: U7.83 (RAS1J), U8.14 (~RAS)
/ISA_386SX_BOARD/RASJ2: U7.82 (RAS2J), U9.14 (~RAS)
/ISA_386SX_BOARD/RASJ3: U7.80 (RAS3J), U12.14 (~RAS)
/ISA_386SX_BOARD/RESETL: CON1.41 (~RESET), U7.120 (RESETLJ)
/ISA_386SX_BOARD/SPKR: R55.1, U7.32 (SPKR)
/ISA_386SX_BOARD/SYSCLK: J13.39, U7.160 (ATCLK)
/ISA_386SX_BOARD/USB_DN: J14.2 (D-)
/ISA_386SX_BOARD/USB_DP: J14.3 (D+)
/ISA_386SX_BOARD/WEJ: U6.13 (~W), U7.79 (WEJ), U8.13 (~W), U9.13 (~W), U12.13 (~W)
/ISA_386SX_BOARD/XD0: U7.136 (XD0), U15.13 (D0)
/ISA_386SX_BOARD/XD1: U7.135 (XD1), U15.14 (D1)
/ISA_386SX_BOARD/XD2: U7.134 (XD2), U15.15 (D2)
/ISA_386SX_BOARD/XD3: U7.133 (XD3), U15.17 (D3)
/ISA_386SX_BOARD/XD4: U7.131 (XD4), U15.18 (D4)
/ISA_386SX_BOARD/XD5: U7.130 (XD5), U15.19 (D5)
/ISA_386SX_BOARD/XD6: U7.129 (XD6), U15.20 (D6)
/ISA_386SX_BOARD/XD7: U7.128 (XD7), U15.21 (D7)
/ISA_386SX_BOARD/~CF_BUSY: CON1.45 (~DASP), R67.2
GND: BT1.2 (-), C29.2, C30.2, C31.2, C32.2, C33.1, C34.1, C35.1, C36.2, C37.2, C38.1, C39.1, C40.1, C41.2, C42.2, C43.1, C44.1, C45.1, C46.1, C47.2, C48.1, C49.1, C50.2, C51.1, C52.1, C53.2, C54.1, C55.1, C56.2, C57.2, C58.1, C59.2, C60.2, C61.1, C62.2, C63.2, C64.1, C65.2, C66.2, C67.1, C68.2, C69.1, C70.1, C71.2, C72.1, C73.1, C74.1, C75.2, C76.1, C77.2, C78.1, C79.2, C80.1, C81.1, C82.2, C83.1, C84.1, C85.1, C86.1, C87.1, C88.1, C89.1, C90.1, C93.1, C94.2, C95.1, C96.2, C97.2, C98.2, C100.1, CON1.1 (GND1), CON1.8 (A10), CON1.9 (~ATASEL), CON1.10 (A9), CON1.11 (A8), CON1.12 (A7), CON1.14 (A6), CON1.15 (A5), CON1.16 (A4), CON1.17 (A3), CON1.39 (~CSEL), CON1.50 (GND2), CON1.S1 (Shield), CON1.S2 (Shield), D4.1 (K), D8.1 (K), J10.1, J10.2, J10.38, J10.40, J11.0, J11.3, J12.0, J12.3, J13.1, J13.61, J13.63, J13.64, J14.4 (GND), J15.2, Q1.2 (E), Q3.3 (C), R25.1, R26.1, R27.1, R28.1, R29.1, R57.2, R58.2, R59.2, R68.2, R71.1, R72.2, R73.1, R74.2, SW2.1, U6.22 (GND), U6.29 (~OE), U6.37 (GND), U6.42 (GND), U7.8 (GND1), U7.31 (GND2), U7.40 (GND3), U7.52 (GND4), U7.65 (GND5), U7.81 (GND6), U7.94 (GND7), U7.104 (GND8), U7.118 (GND9), U7.121 (GND10), U7.132 (GND11), U7.156 (GND12), U7.161 (GND13), U7.169 (GND14), U7.188 (GND15), U7.208 (GND16), U8.22 (GND), U8.29 (~OE), U8.37 (GND), U8.42 (GND), U9.22 (GND), U9.29 (~OE), U9.37 (GND), U9.42 (GND), U10.1, U10.2, U10.4, U10.5, U10.7 (GND), U11.1 (GND), U12.22 (GND), U12.29 (~OE), U12.37 (GND), U12.42 (GND), U13.2 (-), U14.2 (-), U15.16 (GND), U16.2 (GND), U17.1 (GND), U18.3 (GND), X1.2 (GND), X2.2 (GND), Y3.2, Y3.3; also elsewhere on the board
unnamed: BT1.1 (+), D9.2
unnamed: CON1.43 (~INPACK), R58.1
unnamed: D1.1 (K), R66.1
unnamed: D2.1 (K), R67.1
unnamed: D3.1 (K), R68.1
unnamed: C91.2, D4.2 (A), D6.1 (K)
unnamed: C91.1, D5.2 (A), L4.2, U16.1 (SW)
unnamed: D7.2 (A), D8.3 (G), R74.1
unnamed: J9.1, R56.1
unnamed: J9.2, LS1.2
unnamed: J13.59, R65.1
unnamed: J14.5 (Shield), R72.1
unnamed: J15.1, SW3.1 (A)
unnamed: Q1.1 (B), R55.2
unnamed: C31.1, Q1.3 (C), R56.2
unnamed: Q2.1 (B), R57.1, SW1.2
unnamed: C32.1, Q2.3 (C), U11.3 (VCC)
unnamed: Q3.2 (E), R66.2
unnamed: F1.2, SW3.2 (B)
unnamed: R31.1, U7.39 (BCLK2)
unnamed: R30.1, U7.117 (OSC14M)
unnamed: C29.1, R32.1, U7.111 (XTAL1), Y3.1
unnamed: C30.1, R32.2, U7.112 (XTAL2), Y3.4
unnamed: R60.1, SW2.2, U15.30 (A17)
unnamed: C92.2, R70.2, R71.2, U16.3 (FB)
unnamed: R69.2, U16.4 (~SHDN)
unnamed: C99.1, U18.2 (CAP+)
unnamed: C99.2, U18.4 (CAP-)

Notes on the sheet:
40mA
ROM
290mA
R1 may be replaced with two 330k and 180k resistors installed in parallel R5 may be replaced with two 39k and 20k resistors installed in parallel
required to get stable -12V under load
1.1A
300mA
PS/2
RAM 4Mb
Reset
Compact Flash
Beeper
Clock
Power
Optional -5V DC converter
20mA
800mA
100 Ohm
LED
PC/104
